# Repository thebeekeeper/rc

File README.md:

TURBO TORNADO
=============

test

When I was a kid I had a RC car that I really liked to play with, but it pretty rarely worked.  30+ years later I have a couple of decades of experience building embedded systems to control motors and stuff like that so I decided to design replacement electronics for it so my kid can play with it.

To start, I took the top off the car and removed the old PCB.  Here's what we see under there:

We've got leads to the coil that controls steering and some on the other end to the drive motor.  On the bottom there are 6 slots for AA batteries, so I'm assuming the motor and solenoid will work off 9V.  I checked this by connecting a 9V battery to both pairs of leads and saw that the steering and drive motor still work.  To change direction of both actuators, you can just reverse polarity on the battery.

What I really want to do with this project is put a camera where that guys head is supposed to be.  I've always wanted a first person view when driving the car around.

## Parts Selection

The features I'm designing for are:

1. Video streaming to some remote device
2. Wireless control
3. Ability to drive two inductive loads with PWM

I've been using `esp32` devices at work for a while, so I decided on the `ESP32-S3-MINI-1U-N8`.  I found the schematic for the `esp32-cam` board [here](https://github.com/SeeedDocument/forum_doc/blob/master/reg/ESP32_CAM_V1.6.pdf) and it looks pretty straightforward to wire to an FPC connector for a standard camera.  It also supports Bluetooth and WiFi, so I'll have some options for wireless control and video streaming.  I've read that it has issues with video quality when using the chip antenna, so I'll plan on using an external antenna.

To drive the motor and solenoid I was initially planning to build couple of standard H-bridge circuits, but then I found [A3909GLNTR](https://www.digikey.com/en/products/detail/allegro-microsystems/A3909GLNTR-T/3979655) which is an IC with the exact circuit I'd be building anyway so I decided to use that.  I've used some Allegro parts in other designs and they've worked well, so this should be pretty easy.

Got the rev0 boards back an assembled and the drive motor just whines and doesn't turn!  Tried adding some capacitance but that didn't really help.  I can't find any specs for the motor that's installed on the machine so I'm guessing the driver IC isn't able to source the stall current for the motor when it's connected to the gearbox.  I tested the driver with a motor I have lying around with no mechanical load on it and it worked fine.  The `A3909GLNTR` datasheet says you can parallel the outputs to get more current.  Tried that and it starts up the motor and runs no problem.  Added a second driver IC and updated the layout for a rev1 board.

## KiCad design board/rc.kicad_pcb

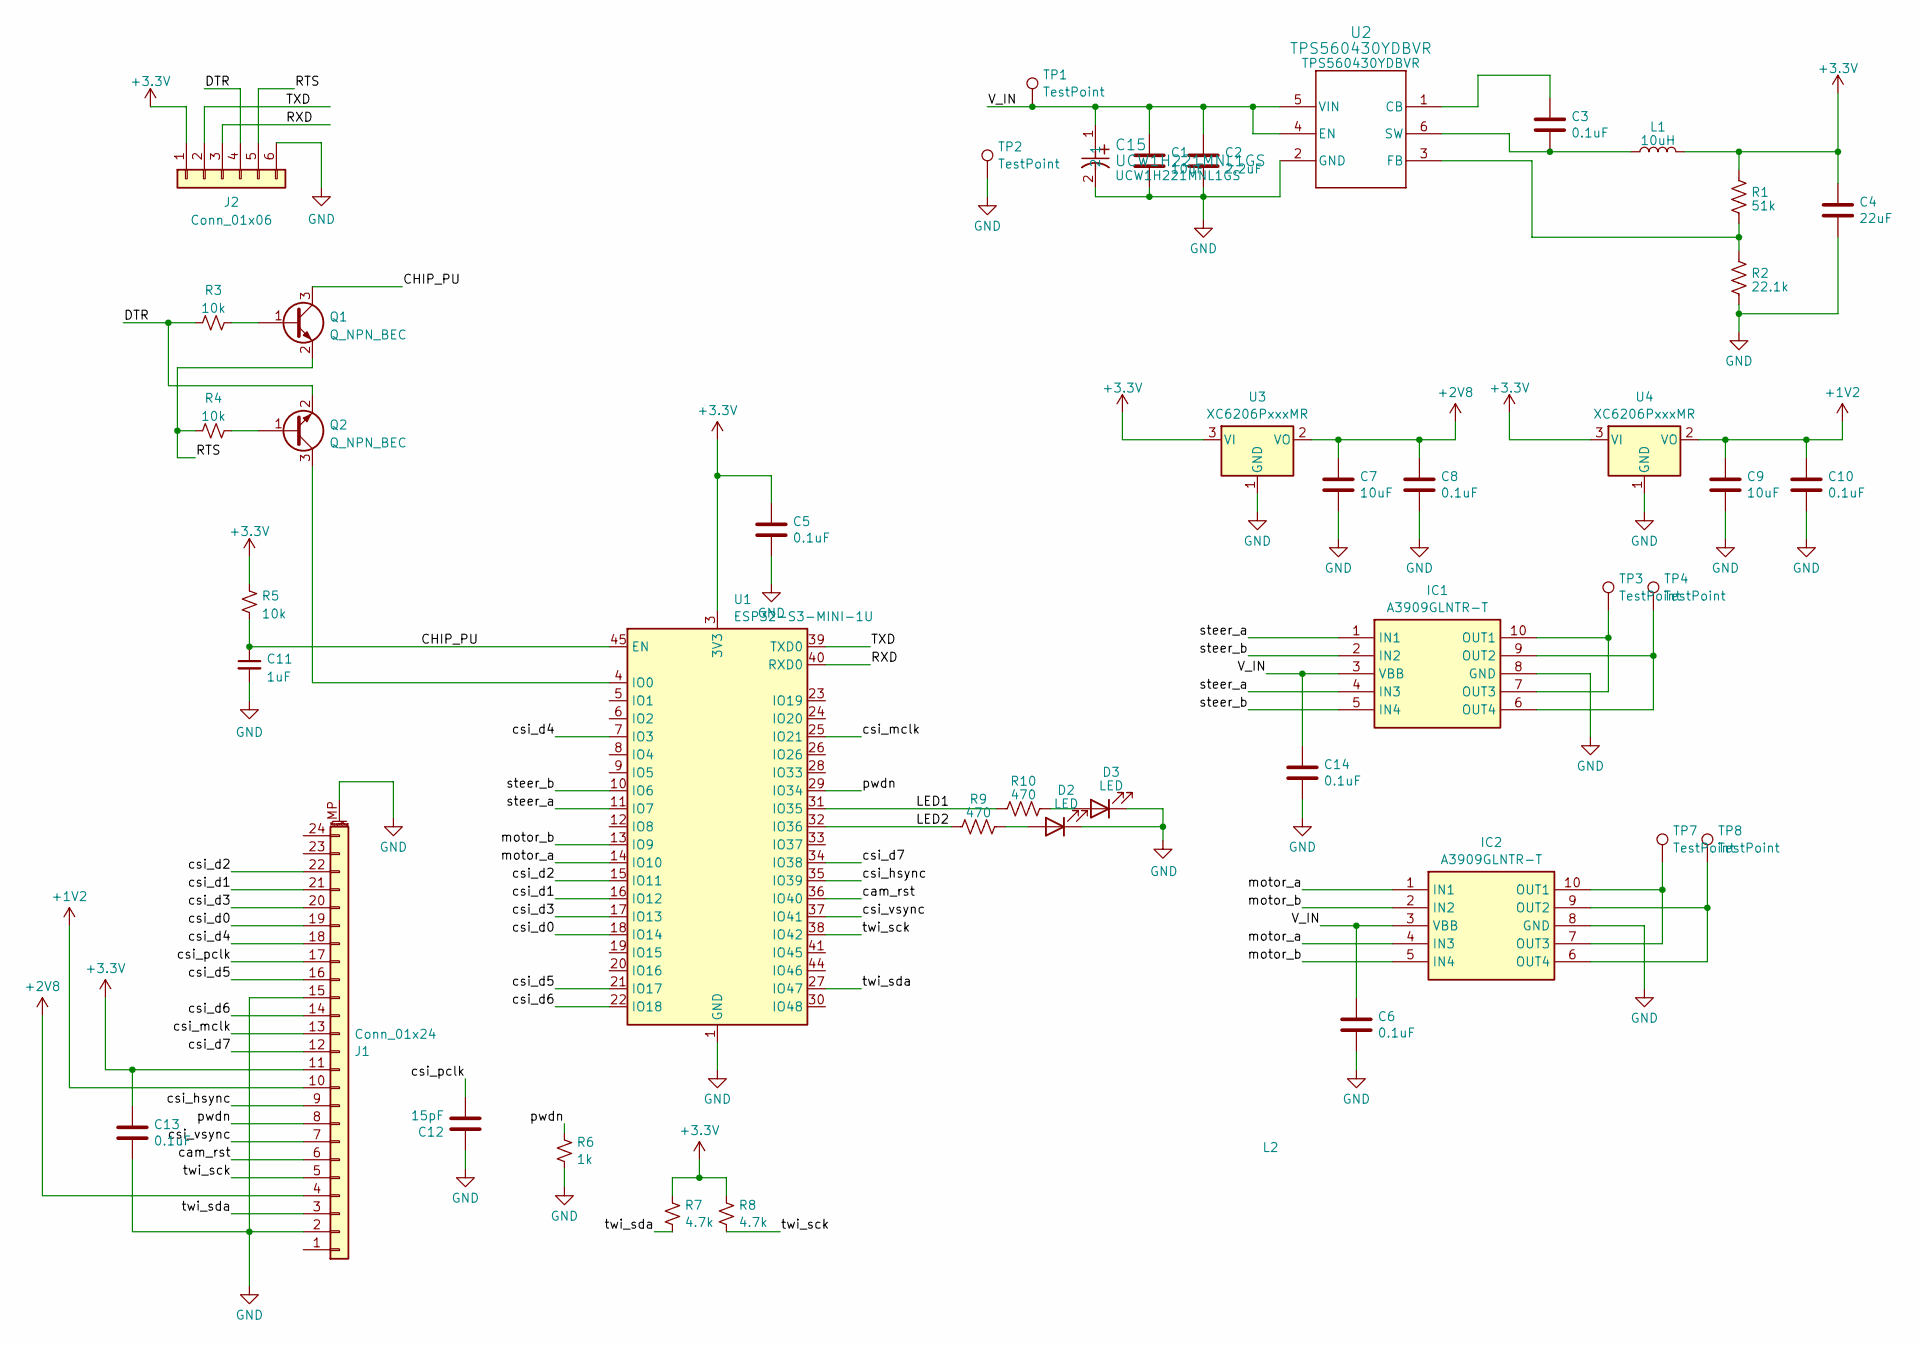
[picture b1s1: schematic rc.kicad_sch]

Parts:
C1: 10uF; C_1206_3216Metric; ManufacturerPartNumber C3216X5R1H106K160AB
C2: 2.2uF; C_0603_1608Metric; ManufacturerPartNumber GRM188R61H225KE11D
C3, C5, C6, C8, C10, C13, C14: 0.1uF; C_0603_1608Metric; ManufacturerPartNumber GRM188R71H104KA93D
C4: 22uF; C_0805_2012Metric; ManufacturerPartNumber C2012X5R1V226M125AC
C7, C9: 10uF; C_0603_1608Metric; ManufacturerPartNumber GRM188R71H104KA93D
C11: 1uF; C_0805_2012Metric; ManufacturerPartNumber CL21B105KOFNFNE
C12: 15pF; C_0603_1608Metric; ManufacturerPartNumber GRM188R71H104KA93D
C15: UCW1H221MNL1GS; ManufacturerPartNumber UCW1H221MNL1GS
D2, D3: LED; LED_0603_1608Metric; ManufacturerPartNumber B1911USD-20D000114U1930
IC1, IC2: A3909GLNTR-T; SOP100P600X175-10N; Mouser Part Number 250-A3909GLNTR-T
J1: Conn_01x24; Hirose_FH12-24S-0.5SH_1x24-1MP_P0.50mm_Horizontal
J2: Conn_01x06; PinHeader_1x06_P2.54mm_Vertical; ManufacturerPartNumber TSW-106-07-G-S
L1: 10uH; SRN3010C2R2M; ManufacturerPartNumber SRN3010C-100M
L2: bird
Q1, Q2: Q_NPN_BEC; SOT-23; ManufacturerPartNumber MMSS8050-H-TP
R1: 51k; R_0805_2012Metric; ManufacturerPartNumber RMCF0805JT51K0
R2: 22.1k; R_0805_2012Metric; ManufacturerPartNumber RMCF0805FT22K1
R3, R4, R5: 10k; R_0805_2012Metric; ManufacturerPartNumber RMCF0805FT10K0
R6: 1k; R_0805_2012Metric; ManufacturerPartNumber RMCF0805FT10K0
R7, R8: 4.7k; R_0805_2012Metric; ManufacturerPartNumber RMCF0805FT10K0
R9, R10: 470; R_0805_2012Metric; ManufacturerPartNumber RC0805FR-07470RL
TP1, TP2, TP3, TP4, TP7, TP8: TestPoint; MountingHole_2.2mm_M2_ISO7380_Pad_TopBottom
U1: ESP32-S3-MINI-1U; ESP32-S2-MINI-1U
U2: TPS560430YDBVR; DBV0006A_L; ManufacturerPartNumber TPS560430YDBVR
U3, U4: XC6206PxxxMR; SOT-23-3

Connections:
+1V2: C9.1, C10.1, J1.10, U4.2 (VO)
+2V8: C7.1, C8.1, J1.4, U3.2 (VO)
+3.3V: C4.1, C5.1, C13.1, J1.11, J2.1, L1.2, R1.2, R5.1, R7.2, R8.2, U1.3 (3V3), U3.3 (VI), U4.3 (VI)
/CHIP_PU: C11.1, Q1.3 (C), R5.2, U1.45 (EN)
/DTR: J2.4, Q2.2 (E), R3.1
/LED1: R10.1, U1.31 (IO35)
/LED2: R9.1, U1.32 (IO36)
/RTS: J2.5, Q1.2 (E), R4.1
/RXD: J2.3, U1.40 (RXD0)
/TXD: J2.2, U1.39 (TXD0)
/V_IN: C1.1, C2.1, C6.1, C14.1, C15.1, IC1.3 (VBB), IC2.3 (VBB), TP1.1, U2.4 (EN), U2.5 (VIN)
/cam_rst: J1.6, U1.36 (IO40)
/csi_d0: J1.19, U1.18 (IO14)
/csi_d1: J1.21, U1.16 (IO12)
/csi_d2: J1.22, U1.15 (IO11)
/csi_d3: J1.20, U1.17 (IO13)
/csi_d4: J1.18, U1.7 (IO3)
/csi_d5: J1.16, U1.21 (IO17)
/csi_d6: J1.14, U1.22 (IO18)
/csi_d7: J1.12, U1.34 (IO38)
/csi_hsync: J1.9, U1.35 (IO39)
/csi_mclk: J1.13, U1.25 (IO21)
/csi_pclk: C12.2, J1.17
/csi_vsync: J1.7, U1.37 (IO41)
/motor_a: IC2.1 (IN1), IC2.4 (IN3), U1.14 (IO10)
/motor_b: IC2.2 (IN2), IC2.5 (IN4), U1.13 (IO9)
/pwdn: J1.8, R6.2, U1.29 (IO34)
/steer_a: IC1.1 (IN1), IC1.4 (IN3), U1.11 (IO7)
/steer_b: IC1.2 (IN2), IC1.5 (IN4), U1.10 (IO6)
/twi_sck: J1.5, R8.1, U1.38 (IO42)
/twi_sda: J1.3, R7.1, U1.27 (IO47)
GND: C1.2, C2.2, C4.2, C5.2, C6.2, C7.2, C8.2, C9.2, C10.2, C11.2, C12.1, C13.2, C14.2, C15.2, D2.1 (K), D3.1 (K), IC1.8 (GND), IC2.8 (GND), J1.2, J1.15, J1.MP (MountPin), J2.6, R2.1, R6.1, TP2.1, U1.1 (GND), U1.2 (GND), U1.42 (GND), U1.43 (GND), U1.46 (GND), U1.47 (GND), U1.48 (GND), U1.49 (GND), U1.50 (GND), U1.51 (GND), U1.52 (GND), U1.53 (GND), U1.54 (GND), U1.55 (GND), U1.56 (GND), U1.57 (GND), U1.58 (GND), U1.59 (GND), U1.60 (GND), U1.61 (GND), U1.62 (GND), U1.63 (GND), U1.64 (GND), U1.65 (GND), U2.2 (GND), U3.1 (GND), U4.1 (GND)
unnamed: D2.2 (A), R9.2
unnamed: D3.2 (A), R10.2
unnamed: IC1.7 (OUT3), IC1.10 (OUT1), TP3.1
unnamed: IC1.6 (OUT4), IC1.9 (OUT2), TP4.1
unnamed: IC2.7 (OUT3), IC2.10 (OUT1), TP7.1
unnamed: IC2.6 (OUT4), IC2.9 (OUT2), TP8.1
unnamed: Q1.1 (B), R3.2
unnamed: Q2.1 (B), R4.2
unnamed: Q2.3 (C), U1.4 (IO0)
unnamed: C3.1, U2.1 (CB)
unnamed: R1.1, R2.2, U2.3 (FB)
unnamed: C3.2, L1.1, U2.6 (SW)

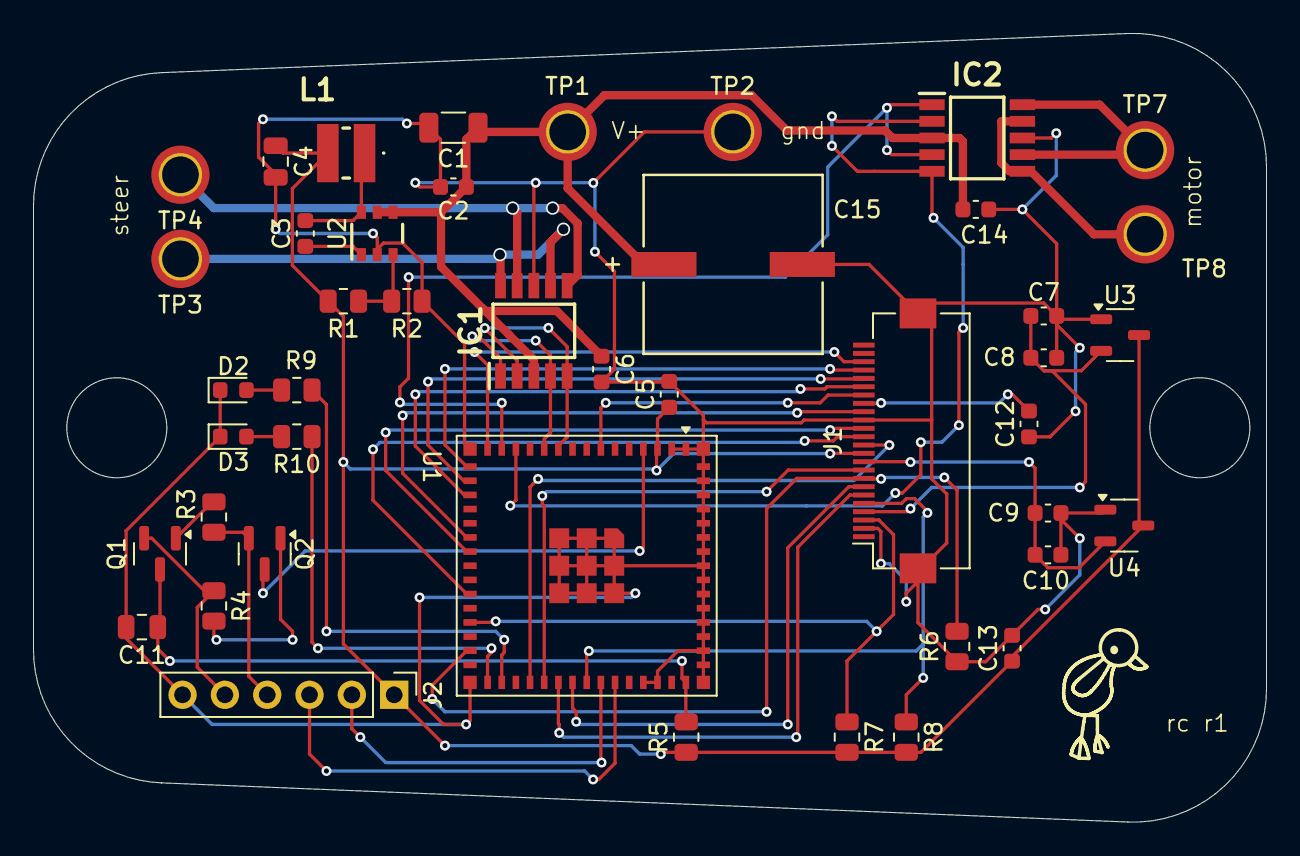
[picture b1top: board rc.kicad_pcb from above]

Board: 2 copper layers, 74.0 x 47.3 mm, 45 parts (0 on the bottom side), 44 nets.

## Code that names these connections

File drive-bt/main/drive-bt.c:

#include <stdio.h>
#include "sdkconfig.h"
#include "freertos/FreeRTOS.h"
#include "freertos/task.h"
#include "esp_system.h"
#include "esp_log.h"
#include "driver/gpio.h"
#include "driver/ledc.h"



#include "nimble/nimble_port.h"
#include "nimble/nimble_port_freertos.h"
#include "host/ble_hs.h"
#include "host/util/util.h"
#include "console/console.h"
#include "services/gap/ble_svc_gap.h"
#include "blecent.h"

#define PWM

#define TAG "drive-bt"

void init_io(void);

#define LED1 GPIO_NUM_35
#define LED2 GPIO_NUM_36

#define STEER_A GPIO_NUM_7
#define STEER_B GPIO_NUM_6
#define MOTOR_A GPIO_NUM_10
#define MOTOR_B GPIO_NUM_9

#define LEDC_TIMER LEDC_TIMER_0
#define LEDC_MODE LEDC_LOW_SPEED_MODE
//#define LEDC_OUTPUT_IO (MOTOR_A) // Define the output GPIO
//#define LEDC_OUTPUT_B (MOTOR_B)
#define MOTOR_A_CHANNEL LEDC_CHANNEL_0
#define MOTOR_B_CHANNEL LEDC_CHANNEL_1
#define STEER_A_CHANNEL LEDC_CHANNEL_2
#define STEER_B_CHANNEL LEDC_CHANNEL_3
#define LEDC_DUTY_RES LEDC_TIMER_13_BIT // Set duty resolution to 13 bits
//#define LEDC_DUTY (1096)                // Set duty to 50%. (2 ** 13) * 50% = 4096
#define LEDC_FREQUENCY (200)            // Frequency in Hertz. Set frequency at 4 kHz

// called from the BLE handler
void update_outputs(int8_t drive, int8_t steer) {
    uint32_t dc = 0;
    if(drive > 10) {
        dc = drive * 53; 
        ESP_LOGI(TAG, "setting drive dc forward: %lu", dc);
        ESP_ERROR_CHECK(ledc_set_duty(LEDC_MODE, MOTOR_A_CHANNEL, dc));
        ESP_ERROR_CHECK(ledc_update_duty(LEDC_MODE, MOTOR_A_CHANNEL));
        // turn off channel B
        ESP_ERROR_CHECK(ledc_set_duty(LEDC_MODE, MOTOR_B_CHANNEL, 0));
        ESP_ERROR_CHECK(ledc_update_duty(LEDC_MODE, MOTOR_B_CHANNEL));
    }
    else if(drive < -10) {
        dc = drive * -53; 
        ESP_LOGI(TAG, "setting drive dc reverse: %lu", dc);
        ESP_ERROR_CHECK(ledc_set_duty(LEDC_MODE, MOTOR_A_CHANNEL, 0));
        ESP_ERROR_CHECK(ledc_update_duty(LEDC_MODE, MOTOR_A_CHANNEL));
        ESP_ERROR_CHECK(ledc_set_duty(LEDC_MODE, MOTOR_B_CHANNEL, dc));
        ESP_ERROR_CHECK(ledc_update_duty(LEDC_MODE, MOTOR_B_CHANNEL));
    }
    else {
        dc = 0;
        ESP_ERROR_CHECK(ledc_set_duty(LEDC_MODE, MOTOR_A_CHANNEL, dc));
        ESP_ERROR_CHECK(ledc_update_duty(LEDC_MODE, MOTOR_A_CHANNEL));
        ESP_ERROR_CHECK(ledc_set_duty(LEDC_MODE, MOTOR_B_CHANNEL, dc));
        ESP_ERROR_CHECK(ledc_update_duty(LEDC_MODE, MOTOR_B_CHANNEL));
    }

    if(steer > 10) {
        //dc = 3000 + (steer * 53); 
        dc = 8192;
        ESP_LOGI(TAG, "setting steer left: %lu", dc);
        ESP_ERROR_CHECK(ledc_set_duty(LEDC_MODE, STEER_A_CHANNEL, dc));
        ESP_ERROR_CHECK(ledc_update_duty(LEDC_MODE, STEER_A_CHANNEL));
        // turn off channel B
        ESP_ERROR_CHECK(ledc_set_duty(LEDC_MODE, STEER_B_CHANNEL, 0));
        ESP_ERROR_CHECK(ledc_update_duty(LEDC_MODE, STEER_B_CHANNEL));
    }
    else if(steer < -10) {
        //dc = steer * 53; 
        dc = 8192;
        ESP_LOGI(TAG, "setting steer right: %lu", dc);
        ESP_ERROR_CHECK(ledc_set_duty(LEDC_MODE, STEER_A_CHANNEL, 0));
        ESP_ERROR_CHECK(ledc_update_duty(LEDC_MODE, STEER_A_CHANNEL));
        ESP_ERROR_CHECK(ledc_set_duty(LEDC_MODE, STEER_B_CHANNEL, dc));
        ESP_ERROR_CHECK(ledc_update_duty(LEDC_MODE, STEER_B_CHANNEL));
    }
    else {
        dc = 0;
        ESP_ERROR_CHECK(ledc_set_duty(LEDC_MODE, STEER_A_CHANNEL, dc));
        ESP_ERROR_CHECK(ledc_update_duty(LEDC_MODE, STEER_A_CHANNEL));
        ESP_ERROR_CHECK(ledc_set_duty(LEDC_MODE, STEER_B_CHANNEL, dc));
        ESP_ERROR_CHECK(ledc_update_duty(LEDC_MODE, STEER_B_CHANNEL));
    }
}


static void example_ledc_init(void)
{
    // Prepare and then apply the LEDC PWM timer configuration
    ledc_timer_config_t ledc_timer = {
        .speed_mode = LEDC_MODE,
        .duty_resolution = LEDC_DUTY_RES,
        .timer_num = LEDC_TIMER,
        .freq_hz = LEDC_FREQUENCY, // Set output frequency at 4 kHz
        .clk_cfg = LEDC_AUTO_CLK};
    ESP_ERROR_CHECK(ledc_timer_config(&ledc_timer));

    // Prepare and then apply the LEDC PWM channel configuration
    ledc_channel_config_t ledc_channel = {
        .speed_mode = LEDC_MODE,
        .channel = MOTOR_A_CHANNEL,
        .timer_sel = LEDC_TIMER,
        .intr_type = LEDC_INTR_DISABLE,
        .gpio_num = MOTOR_A,
        .duty = 0, // Set duty to 0%
        .hpoint = 0};
    ESP_ERROR_CHECK(ledc_channel_config(&ledc_channel));

    ledc_channel_config_t ledc_channel_b = {
        .speed_mode = LEDC_MODE,
        .channel = MOTOR_B_CHANNEL,
        .timer_sel = LEDC_TIMER,
        .intr_type = LEDC_INTR_DISABLE,
        .gpio_num = MOTOR_B,
        .duty = 0, // Set duty to 0%
        .hpoint = 0};
    ESP_ERROR_CHECK(ledc_channel_config(&ledc_channel_b));

    ledc_channel_config_t ledc_channel_c = {
        .speed_mode = LEDC_MODE,
        .channel = STEER_A_CHANNEL,
        .timer_sel = LEDC_TIMER,
        .intr_type = LEDC_INTR_DISABLE,
        .gpio_num = STEER_A,
        .duty = 0, // Set duty to 0%
        .hpoint = 0};
    ESP_ERROR_CHECK(ledc_channel_config(&ledc_channel_c));

    ledc_channel_config_t ledc_channel_d = {
        .speed_mode = LEDC_MODE,
        .channel = STEER_B_CHANNEL,
        .timer_sel = LEDC_TIMER,
        .intr_type = LEDC_INTR_DISABLE,
        .gpio_num = STEER_B,
        .duty = 0, // Set duty to 0%
        .hpoint = 0};
    ESP_ERROR_CHECK(ledc_channel_config(&ledc_channel_d));
}

void app_main(void)
{
    ESP_LOGI(TAG, "hello");
    init_io();

    uint8_t led = 1;
    //gpio_set_level(MOTOR_A, 0);
    //gpio_set_level(MOTOR_B, 0);

    //gpio_set_level(STEER_A, 0);
    //gpio_set_level(STEER_B, 0);

#ifdef PWM
    // Set the LEDC peripheral configuration
    example_ledc_init();
    init_ble();
#endif

    while (1)
    {
        gpio_set_level(LED1, led);
        gpio_set_level(LED2, !led);
        // useful for testing hardware
#ifndef PWM
        gpio_set_level(STEER_A, led);
        gpio_set_level(STEER_B, !led);
        gpio_set_level(MOTOR_A, led);
        gpio_set_level(MOTOR_B, !led);
#endif
        led = !led;
        vTaskDelay(1000 / portTICK_PERIOD_MS);
    }
}

void init_io(void)
{
    gpio_config_t io_conf = {};
    io_conf.intr_type = GPIO_INTR_DISABLE;
    io_conf.mode = GPIO_MODE_OUTPUT;
    io_conf.pin_bit_mask = (1ULL << LED1);
    io_conf.pull_down_en = 0;
    io_conf.pull_up_en = 0;
    gpio_config(&io_conf);
    io_conf.pin_bit_mask = (1ULL << LED2);
    gpio_config(&io_conf);
#ifndef PWM
    io_conf.pin_bit_mask = (1ULL << STEER_A);
    gpio_config(&io_conf);
    io_conf.pin_bit_mask = (1ULL << STEER_B);
    gpio_config(&io_conf);
    io_conf.pin_bit_mask = (1ULL << MOTOR_A);
    gpio_config(&io_conf);
    io_conf.pin_bit_mask = (1ULL << MOTOR_B);
    gpio_config(&io_conf);
#endif
}

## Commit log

2024-09-11 initial pcb design
2024-09-11 Added readme
2024-09-11 Readme
2024-09-15 joystick firmware
2024-09-20 added initial firmware project
2024-09-22 added another motor driver, made mounting holes smaller, added cap for input voltage
2024-09-23 Test
2024-10-06 brought in example ble central code
2024-10-06 can control drive motor from BT joystick
2024-10-09 set up pwm for motor and steering outputs
2024-10-09 fixed some logic bugs with the motor control
